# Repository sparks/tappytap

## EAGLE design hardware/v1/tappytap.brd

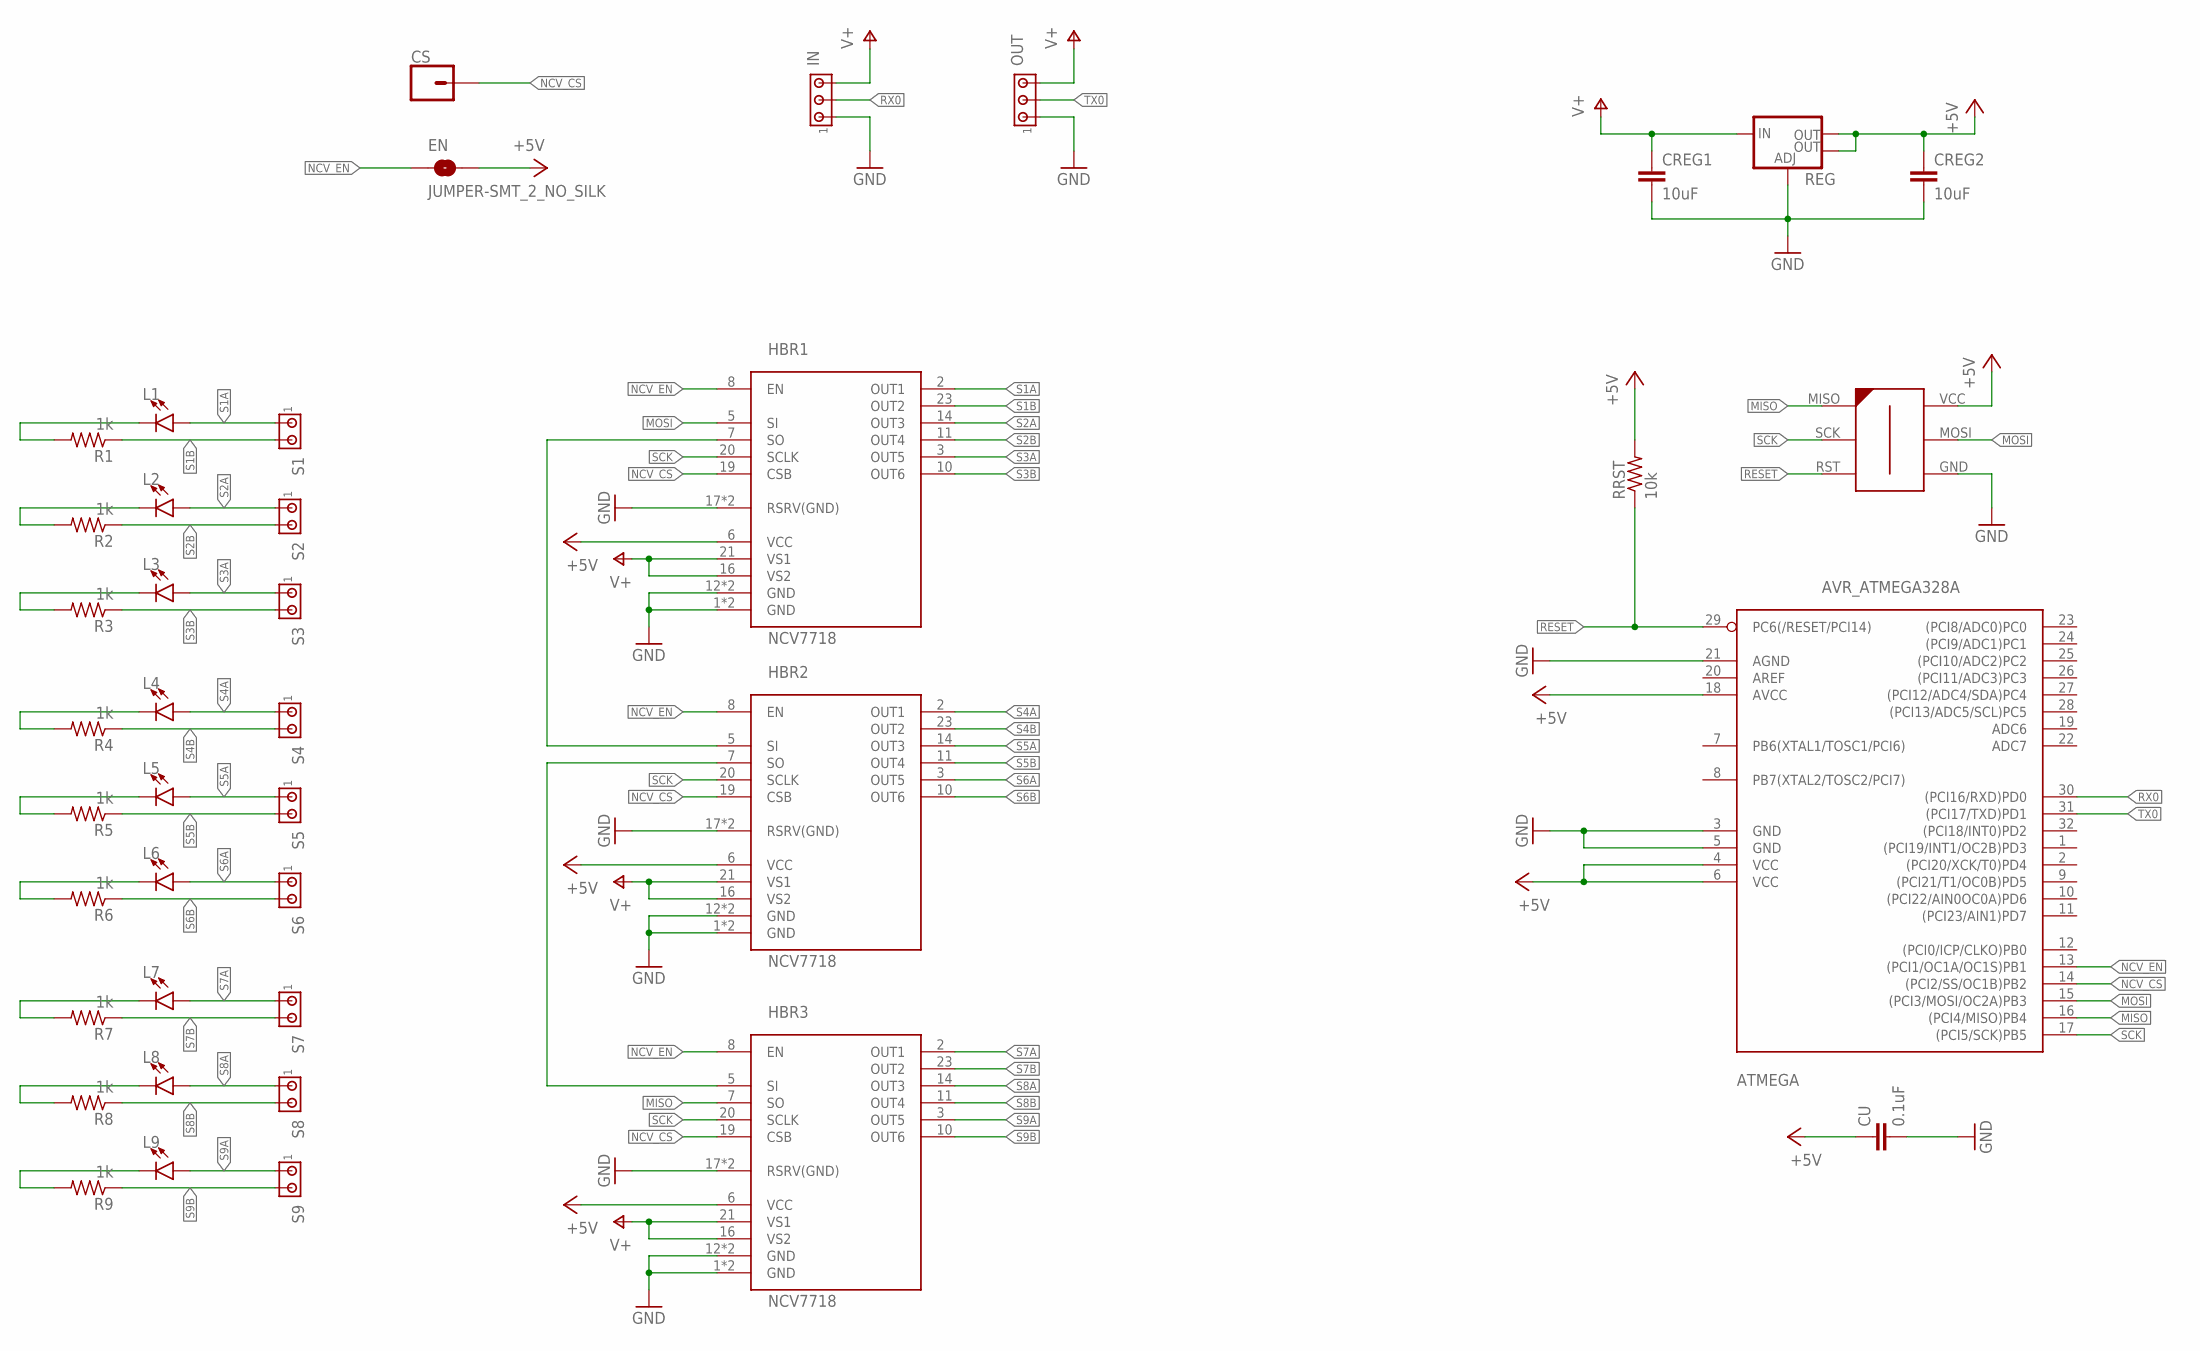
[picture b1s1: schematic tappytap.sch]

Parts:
ATMEGA: AVR_ATMEGA328A; AVR_TQFP32-08
CREG1, CREG2: 10uF; C0603
CS: CONN_01; 1X01
CU: 0.1uF; C0603
EN: JUMPER-SMT_2_NO_SILK; SMT-JUMPER_2_NO_SILK
HBR1, HBR2, HBR3: NCV7718; 24-SSOP
IN: MTA03-100; 10X03MTA
ISP: AVR-ISP-6-EDGE; 6PAD_ISP
L1, L2, L3, L4, L5, L6, L7, L8, L9: LED0603; LED-0603
OUT: MTA03-100; 10X03MTA
R1, R2, R3, R4, R5, R6, R7, R8, R9: 1k; R0603
REG: V_REG_LM1117SOT223; SOT223
RRST: 10k; R0603
S1, S2, S3, S4, S5, S6, S7, S8, S9: MTA02-100; 10X02MTA

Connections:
+5V: ATMEGA.4 (VCC), ATMEGA.6 (VCC), ATMEGA.18 (AVCC), CREG2.1, CU.1, EN.2, HBR1.6 (VCC), HBR2.6 (VCC), HBR3.6 (VCC), ISP.VCC, REG.2 (OUT), REG.4 (OUT), RRST.2
GND: ATMEGA.3 (GND), ATMEGA.5 (GND), ATMEGA.21 (AGND), CREG1.2, CREG2.2, CU.2, HBR1.1 (GND), HBR1.12 (GND), HBR1.13 (GND), HBR1.17 (RSRV(GND)), HBR1.18 (RSRV(GND)), HBR1.24 (GND), HBR2.1 (GND), HBR2.12 (GND), HBR2.13 (GND), HBR2.17 (RSRV(GND)), HBR2.18 (RSRV(GND)), HBR2.24 (GND), HBR3.1 (GND), HBR3.12 (GND), HBR3.13 (GND), HBR3.17 (RSRV(GND)), HBR3.18 (RSRV(GND)), HBR3.24 (GND), IN.1, ISP.GND, OUT.1, REG.1 (ADJ)
MISO: ATMEGA.16 ((PCI4/MISO)PB4), HBR3.7 (SO), ISP.MISO
MOSI: ATMEGA.15 ((PCI3/MOSI/OC2A)PB3), HBR1.5 (SI), ISP.MOSI
unnamed: L1.C, R1.2
unnamed: L2.C, R2.2
unnamed: L3.C, R3.2
unnamed: L4.C, R4.2
unnamed: L5.C, R5.2
unnamed: L6.C, R6.2
unnamed: HBR1.7 (SO), HBR2.5 (SI)
unnamed: L7.C, R7.2
unnamed: HBR2.7 (SO), HBR3.5 (SI)
unnamed: L8.C, R8.2
unnamed: L9.C, R9.2
NCV_CS: ATMEGA.14 ((PCI2/SS/OC1B)PB2), CS.1, HBR1.19 (CSB), HBR2.19 (CSB), HBR3.19 (CSB)
NCV_EN: ATMEGA.13 ((PCI1/OC1A/OC1S)PB1), EN.1, HBR1.8 (EN), HBR2.8 (EN), HBR3.8 (EN)
RESET: ATMEGA.29 (PC6(/RESET/PCI14)), ISP.RST, RRST.1
RX0: ATMEGA.30 ((PCI16/RXD)PD0), IN.2
S1A: HBR1.2 (OUT1), L1.A, S1.1
S1B: HBR1.23 (OUT2), R1.1, S1.2
S2A: HBR1.14 (OUT3), L2.A, S2.1
S2B: HBR1.11 (OUT4), R2.1, S2.2
S3A: HBR1.3 (OUT5), L3.A, S3.1
S3B: HBR1.10 (OUT6), R3.1, S3.2
S4A: HBR2.2 (OUT1), L4.A, S4.1
S4B: HBR2.23 (OUT2), R4.1, S4.2
S5A: HBR2.14 (OUT3), L5.A, S5.1
S5B: HBR2.11 (OUT4), R5.1, S5.2
S6A: HBR2.3 (OUT5), L6.A, S6.1
S6B: HBR2.10 (OUT6), R6.1, S6.2
S7A: HBR3.2 (OUT1), L7.A, S7.1
S7B: HBR3.23 (OUT2), R7.1, S7.2
S8A: HBR3.14 (OUT3), L8.A, S8.1
S8B: HBR3.11 (OUT4), R8.1, S8.2
S9A: HBR3.3 (OUT5), L9.A, S9.1
S9B: HBR3.10 (OUT6), R9.1, S9.2
SCK: ATMEGA.17 ((PCI5/SCK)PB5), HBR1.20 (SCLK), HBR2.20 (SCLK), HBR3.20 (SCLK), ISP.SCK
TX0: ATMEGA.31 ((PCI17/TXD)PD1), OUT.2
V+: CREG1.1, HBR1.16 (VS2), HBR1.21 (VS1), HBR2.16 (VS2), HBR2.21 (VS1), HBR3.16 (VS2), HBR3.21 (VS1), IN.3, OUT.3, REG.3 (IN)

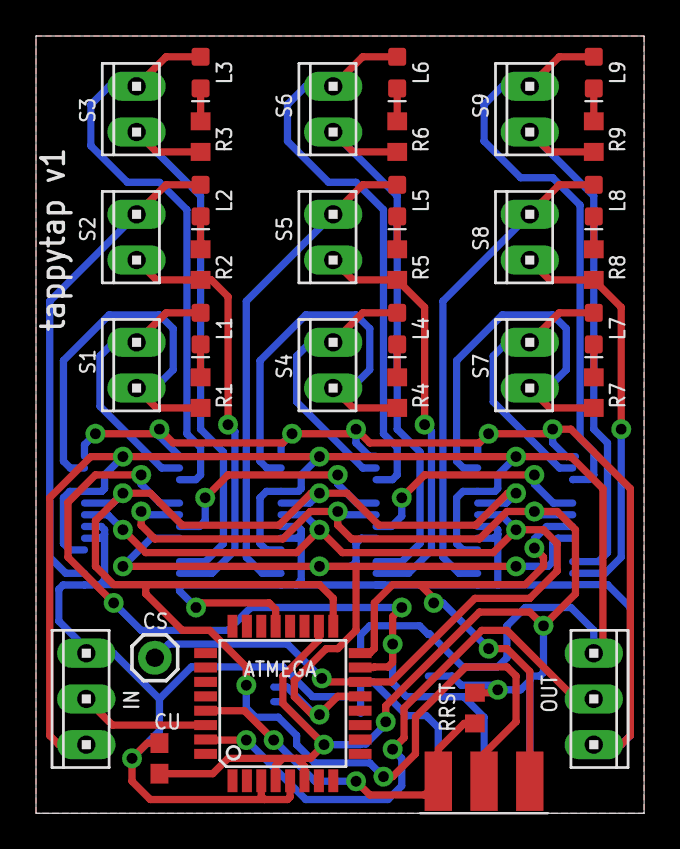
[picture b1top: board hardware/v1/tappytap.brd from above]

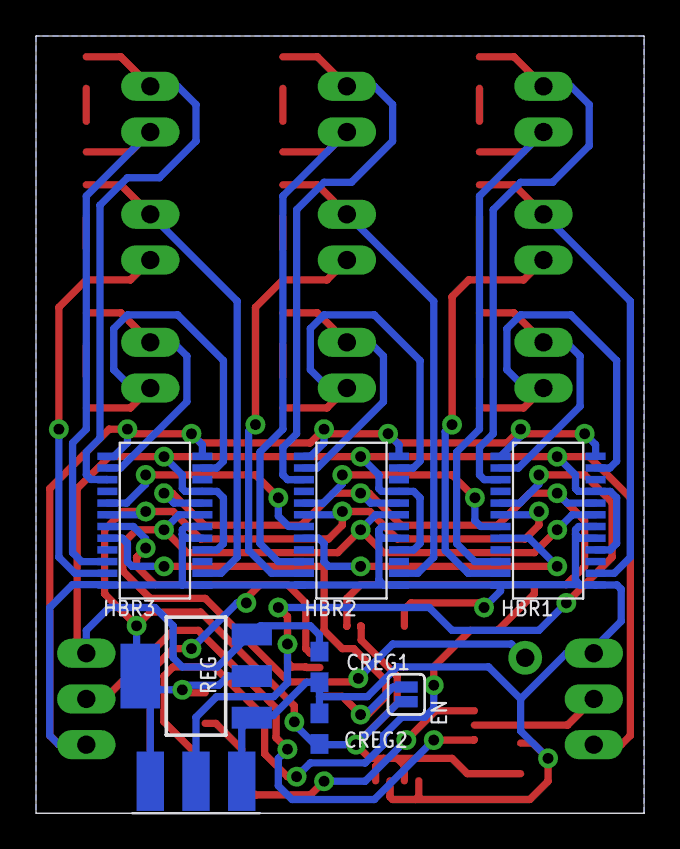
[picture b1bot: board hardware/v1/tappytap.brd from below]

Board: 2 copper layers, 33.8 x 43.2 mm, 41 parts (7 on the bottom side), 40 nets.

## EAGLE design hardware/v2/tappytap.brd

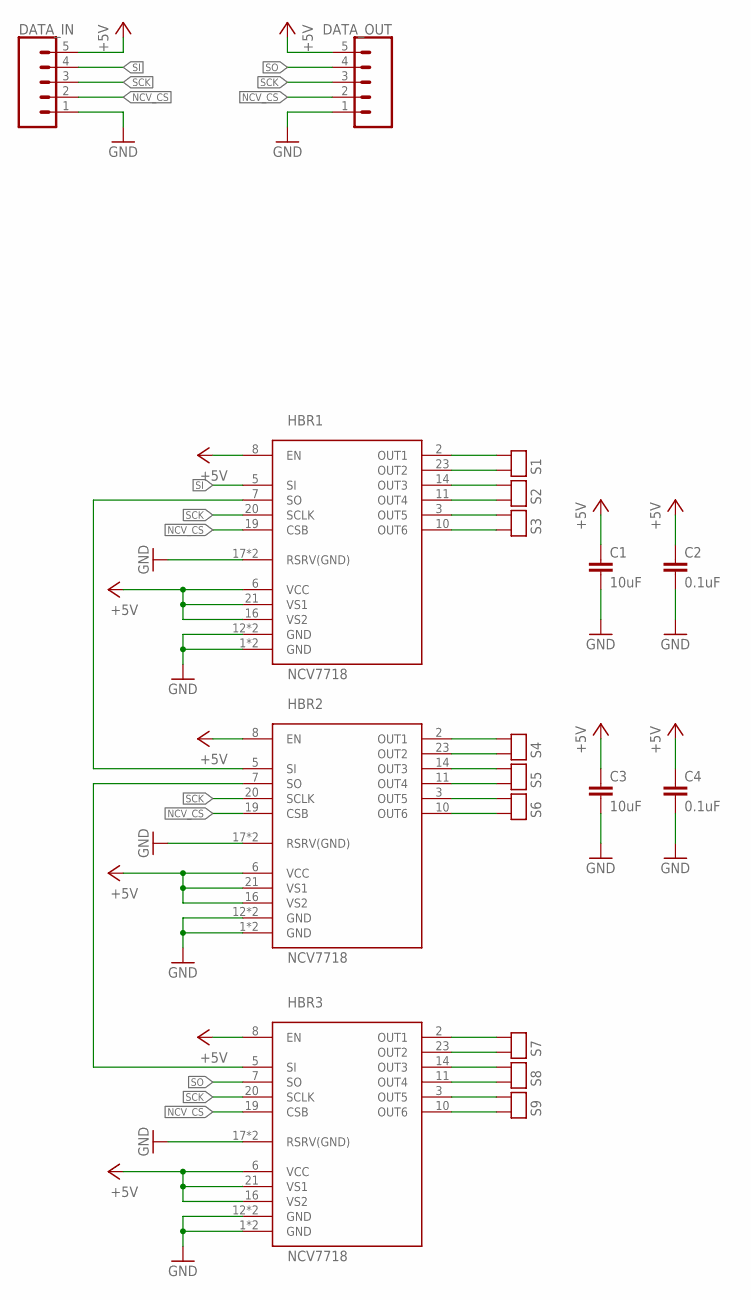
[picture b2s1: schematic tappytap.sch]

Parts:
C1, C3: 10uF; C0603
C2, C4: 0.1uF; C0603
DATA_IN: CONN_05; 1X05
DATA_OUT: CONN_05; 1X05
HBR1, HBR2, HBR3: NCV7718; 24-SSOP
S1, S2, S3, S4, S5, S6, S7, S8, S9: TP2; TP2_2MM

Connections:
+5V: C1.1, C2.1, C3.1, C4.1, DATA_IN.5, DATA_OUT.5, HBR1.6 (VCC), HBR1.8 (EN), HBR1.16 (VS2), HBR1.21 (VS1), HBR2.6 (VCC), HBR2.8 (EN), HBR2.16 (VS2), HBR2.21 (VS1), HBR3.6 (VCC), HBR3.8 (EN), HBR3.16 (VS2), HBR3.21 (VS1)
GND: C1.2, C2.2, C3.2, C4.2, DATA_IN.1, DATA_OUT.1, HBR1.1 (GND), HBR1.12 (GND), HBR1.13 (GND), HBR1.17 (RSRV(GND)), HBR1.18 (RSRV(GND)), HBR1.24 (GND), HBR2.1 (GND), HBR2.12 (GND), HBR2.13 (GND), HBR2.17 (RSRV(GND)), HBR2.18 (RSRV(GND)), HBR2.24 (GND), HBR3.1 (GND), HBR3.12 (GND), HBR3.13 (GND), HBR3.17 (RSRV(GND)), HBR3.18 (RSRV(GND)), HBR3.24 (GND)
unnamed: HBR1.7 (SO), HBR2.5 (SI)
unnamed: HBR2.7 (SO), HBR3.5 (SI)
NCV_CS: DATA_IN.2, DATA_OUT.2, HBR1.19 (CSB), HBR2.19 (CSB), HBR3.19 (CSB)
S1A: HBR1.2 (OUT1), S1.P$1 (0)
S1B: HBR1.23 (OUT2), S1.P$2 (1)
S2A: HBR1.14 (OUT3), S2.P$1 (0)
S2B: HBR1.11 (OUT4), S2.P$2 (1)
S3A: HBR1.3 (OUT5), S3.P$1 (0)
S3B: HBR1.10 (OUT6), S3.P$2 (1)
S4A: HBR2.2 (OUT1), S4.P$1 (0)
S4B: HBR2.23 (OUT2), S4.P$2 (1)
S5A: HBR2.14 (OUT3), S5.P$1 (0)
S5B: HBR2.11 (OUT4), S5.P$2 (1)
S6A: HBR2.3 (OUT5), S6.P$1 (0)
S6B: HBR2.10 (OUT6), S6.P$2 (1)
S7A: HBR3.2 (OUT1), S7.P$1 (0)
S7B: HBR3.23 (OUT2), S7.P$2 (1)
S8A: HBR3.14 (OUT3), S8.P$1 (0)
S8B: HBR3.11 (OUT4), S8.P$2 (1)
S9A: HBR3.3 (OUT5), S9.P$1 (0)
S9B: HBR3.10 (OUT6), S9.P$2 (1)
SCK: DATA_IN.3, DATA_OUT.3, HBR1.20 (SCLK), HBR2.20 (SCLK), HBR3.20 (SCLK)
SI: DATA_IN.4, HBR1.5 (SI)
SO: DATA_OUT.4, HBR3.7 (SO)

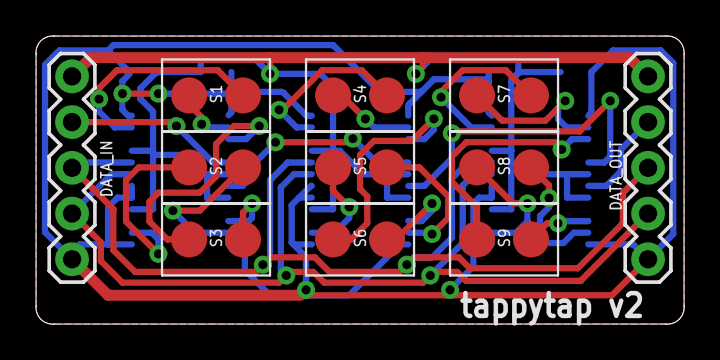
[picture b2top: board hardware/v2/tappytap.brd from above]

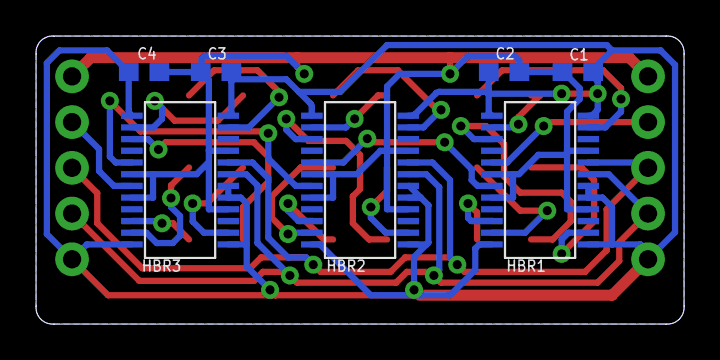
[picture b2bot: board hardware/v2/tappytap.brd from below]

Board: 2 copper layers, 36.0 x 16.0 mm, 18 parts (7 on the bottom side), 26 nets.

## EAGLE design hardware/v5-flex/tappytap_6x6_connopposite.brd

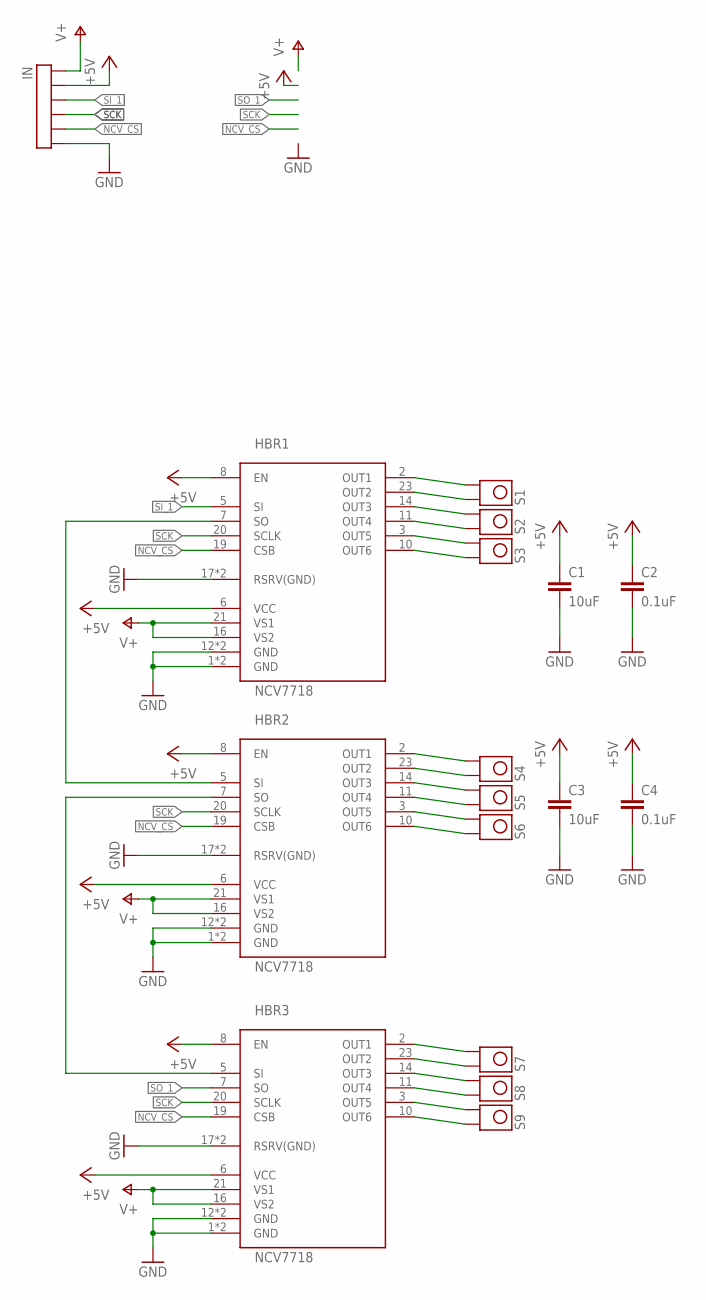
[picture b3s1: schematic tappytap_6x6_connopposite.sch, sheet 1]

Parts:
C1, C3: 10uF; C0603
C2, C4: 0.1uF; C0603
HBR1, HBR2, HBR3: NCV7718; SSOP-24
IN: TP6; TP6_2MM
S1, S2, S3, S4, S5, S6, S7, S8, S9: TP_6MM_BIG_PAD

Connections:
+5V: C1.1, C2.1, C3.1, C4.1, HBR1.6 (VCC), HBR1.8 (EN), HBR2.6 (VCC), HBR2.8 (EN), HBR3.6 (VCC), HBR3.8 (EN), IN.P$5 (5); also elsewhere on the board
GND: C1.2, C2.2, C3.2, C4.2, HBR1.1 (GND), HBR1.12 (GND), HBR1.13 (GND), HBR1.17 (RSRV(GND)), HBR1.18 (RSRV(GND)), HBR1.24 (GND), HBR2.1 (GND), HBR2.12 (GND), HBR2.13 (GND), HBR2.17 (RSRV(GND)), HBR2.18 (RSRV(GND)), HBR2.24 (GND), HBR3.1 (GND), HBR3.12 (GND), HBR3.13 (GND), HBR3.17 (RSRV(GND)), HBR3.18 (RSRV(GND)), HBR3.24 (GND), IN.P$1 (1); also elsewhere on the board
unnamed: HBR1.7 (SO), HBR2.5 (SI)
unnamed: HBR2.7 (SO), HBR3.5 (SI)
NCV_CS: HBR1.19 (CSB), HBR2.19 (CSB), HBR3.19 (CSB), IN.P$2 (2); also elsewhere on the board
S1A: HBR1.2 (OUT1), S1.P$1 (0)
S1B: HBR1.23 (OUT2), S1.P$2 (1)
S2A: HBR1.14 (OUT3), S2.P$1 (0)
S2B: HBR1.11 (OUT4), S2.P$2 (1)
S3A: HBR1.3 (OUT5), S3.P$1 (0)
S3B: HBR1.10 (OUT6), S3.P$2 (1)
S4A: HBR2.2 (OUT1), S4.P$1 (0)
S4B: HBR2.23 (OUT2), S4.P$2 (1)
S5A: HBR2.14 (OUT3), S5.P$1 (0)
S5B: HBR2.11 (OUT4), S5.P$2 (1)
S6A: HBR2.3 (OUT5), S6.P$1 (0)
S6B: HBR2.10 (OUT6), S6.P$2 (1)
S7A: HBR3.2 (OUT1), S7.P$1 (0)
S7B: HBR3.23 (OUT2), S7.P$2 (1)
S8A: HBR3.14 (OUT3), S8.P$1 (0)
S8B: HBR3.11 (OUT4), S8.P$2 (1)
S9A: HBR3.3 (OUT5), S9.P$1 (0)
S9B: HBR3.10 (OUT6), S9.P$2 (1)
SCK: HBR1.20 (SCLK), HBR2.20 (SCLK), HBR3.20 (SCLK), IN.P$3 (3); also elsewhere on the board
SI_1: HBR1.5 (SI), IN.P$4 (4)
SO_1: HBR3.7 (SO); also elsewhere on the board
V+: HBR1.16 (VS2), HBR1.21 (VS1), HBR2.16 (VS2), HBR2.21 (VS1), HBR3.16 (VS2), HBR3.21 (VS1), IN.P$6 (6); also elsewhere on the board

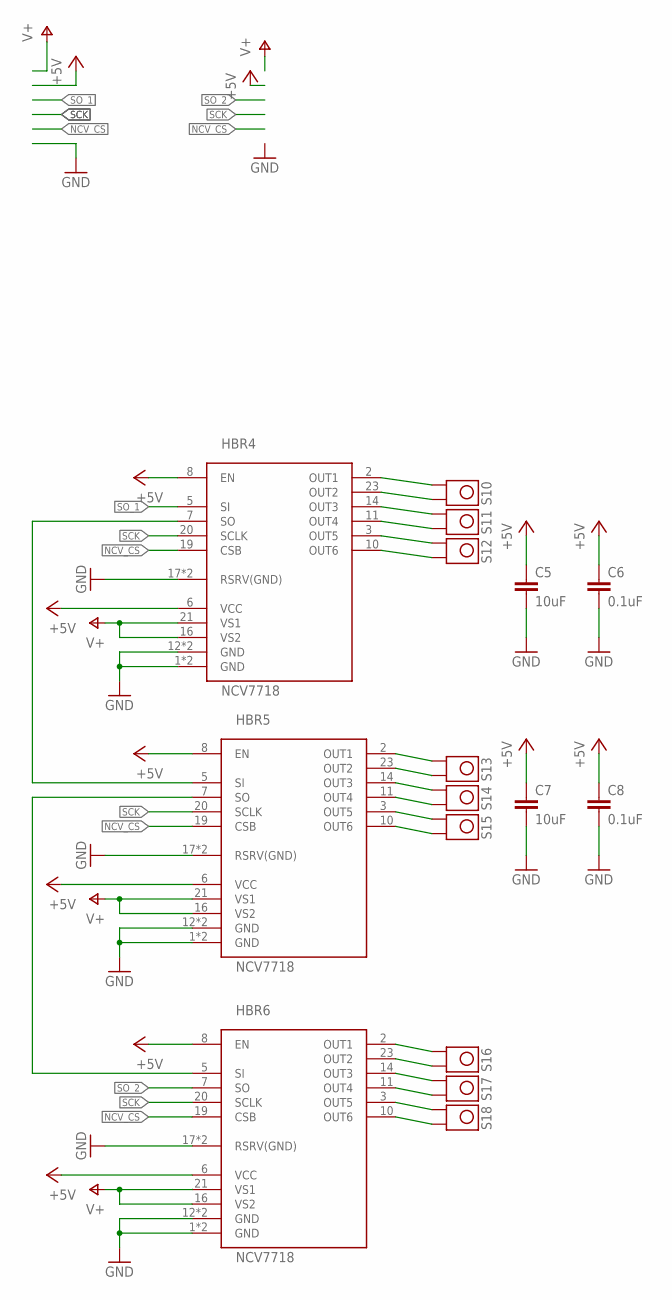
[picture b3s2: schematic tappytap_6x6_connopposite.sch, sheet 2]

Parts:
C5, C7: 10uF; C0603
C6, C8: 0.1uF; C0603
HBR4, HBR5, HBR6: NCV7718; SSOP-24
S10, S11, S12, S13, S14, S15, S16, S17, S18: TP_6MM_BIG_PAD

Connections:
+5V: C5.1, C6.1, C7.1, C8.1, HBR4.6 (VCC), HBR4.8 (EN), HBR5.6 (VCC), HBR5.8 (EN), HBR6.6 (VCC), HBR6.8 (EN); also elsewhere on the board
GND: C5.2, C6.2, C7.2, C8.2, HBR4.1 (GND), HBR4.12 (GND), HBR4.13 (GND), HBR4.17 (RSRV(GND)), HBR4.18 (RSRV(GND)), HBR4.24 (GND), HBR5.1 (GND), HBR5.12 (GND), HBR5.13 (GND), HBR5.17 (RSRV(GND)), HBR5.18 (RSRV(GND)), HBR5.24 (GND), HBR6.1 (GND), HBR6.12 (GND), HBR6.13 (GND), HBR6.17 (RSRV(GND)), HBR6.18 (RSRV(GND)), HBR6.24 (GND); also elsewhere on the board
unnamed: HBR4.7 (SO), HBR5.5 (SI)
unnamed: HBR5.7 (SO), HBR6.5 (SI)
NCV_CS: HBR4.19 (CSB), HBR5.19 (CSB), HBR6.19 (CSB); also elsewhere on the board
S1A1: HBR4.2 (OUT1), S10.P$1 (0)
S1B1: HBR4.23 (OUT2), S10.P$2 (1)
S2A1: HBR4.14 (OUT3), S11.P$1 (0)
S2B1: HBR4.11 (OUT4), S11.P$2 (1)
S3A1: HBR4.3 (OUT5), S12.P$1 (0)
S3B1: HBR4.10 (OUT6), S12.P$2 (1)
S4A1: HBR5.2 (OUT1), S13.P$1 (0)
S4B1: HBR5.23 (OUT2), S13.P$2 (1)
S5A1: HBR5.14 (OUT3), S14.P$1 (0)
S5B1: HBR5.11 (OUT4), S14.P$2 (1)
S6A1: HBR5.3 (OUT5), S15.P$1 (0)
S6B1: HBR5.10 (OUT6), S15.P$2 (1)
S7A1: HBR6.2 (OUT1), S16.P$1 (0)
S7B1: HBR6.23 (OUT2), S16.P$2 (1)
S8A1: HBR6.14 (OUT3), S17.P$1 (0)
S8B1: HBR6.11 (OUT4), S17.P$2 (1)
S9A1: HBR6.3 (OUT5), S18.P$1 (0)
S9B1: HBR6.10 (OUT6), S18.P$2 (1)
SCK: HBR4.20 (SCLK), HBR5.20 (SCLK), HBR6.20 (SCLK); also elsewhere on the board
SO_1: HBR4.5 (SI); also elsewhere on the board
SO_2: HBR6.7 (SO); also elsewhere on the board
V+: HBR4.16 (VS2), HBR4.21 (VS1), HBR5.16 (VS2), HBR5.21 (VS1), HBR6.16 (VS2), HBR6.21 (VS1); also elsewhere on the board

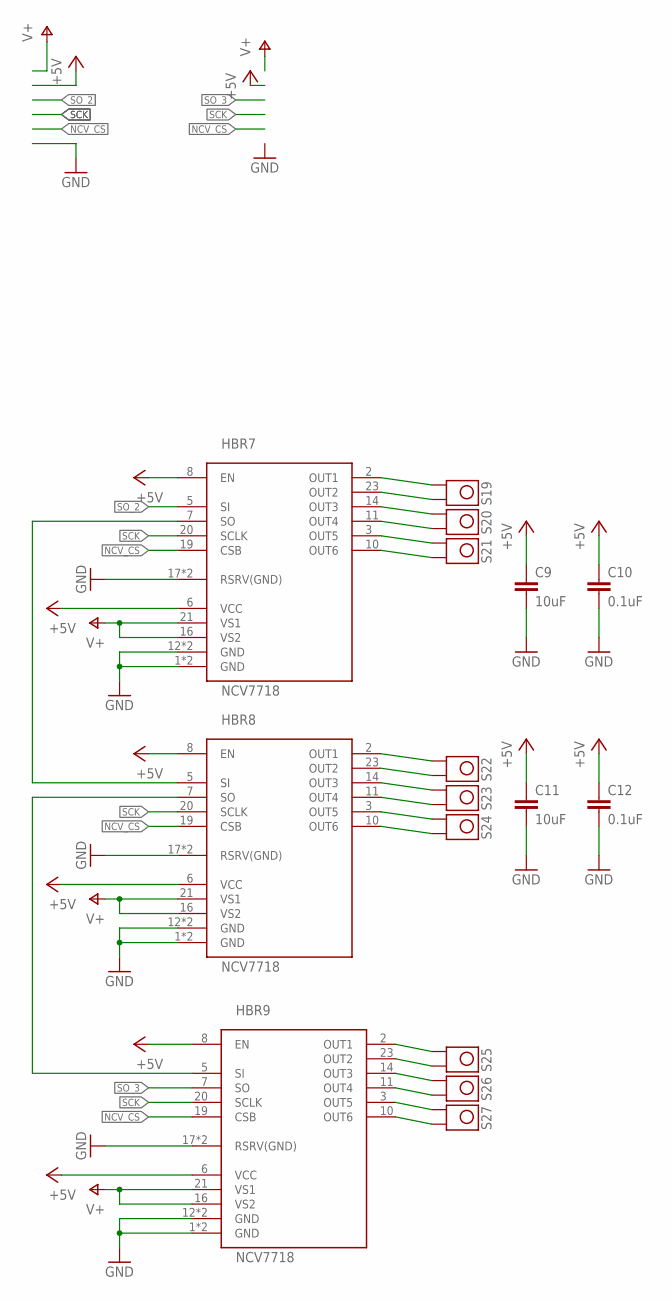
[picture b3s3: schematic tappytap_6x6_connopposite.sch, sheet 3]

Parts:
C9, C11: 10uF; C0603
C10, C12: 0.1uF; C0603
HBR7, HBR8, HBR9: NCV7718; SSOP-24
S19, S20, S21, S22, S23, S24, S25, S26, S27: TP_6MM_BIG_PAD

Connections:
+5V: C9.1, C10.1, C11.1, C12.1, HBR7.6 (VCC), HBR7.8 (EN), HBR8.6 (VCC), HBR8.8 (EN), HBR9.6 (VCC), HBR9.8 (EN); also elsewhere on the board
GND: C9.2, C10.2, C11.2, C12.2, HBR7.1 (GND), HBR7.12 (GND), HBR7.13 (GND), HBR7.17 (RSRV(GND)), HBR7.18 (RSRV(GND)), HBR7.24 (GND), HBR8.1 (GND), HBR8.12 (GND), HBR8.13 (GND), HBR8.17 (RSRV(GND)), HBR8.18 (RSRV(GND)), HBR8.24 (GND), HBR9.1 (GND), HBR9.12 (GND), HBR9.13 (GND), HBR9.17 (RSRV(GND)), HBR9.18 (RSRV(GND)), HBR9.24 (GND); also elsewhere on the board
unnamed: HBR7.7 (SO), HBR8.5 (SI)
unnamed: HBR8.7 (SO), HBR9.5 (SI)
NCV_CS: HBR7.19 (CSB), HBR8.19 (CSB), HBR9.19 (CSB); also elsewhere on the board
S1A2: HBR7.2 (OUT1), S19.P$1 (0)
S1B2: HBR7.23 (OUT2), S19.P$2 (1)
S2A2: HBR7.14 (OUT3), S20.P$1 (0)
S2B2: HBR7.11 (OUT4), S20.P$2 (1)
S3A2: HBR7.3 (OUT5), S21.P$1 (0)
S3B2: HBR7.10 (OUT6), S21.P$2 (1)
S4A2: HBR8.2 (OUT1), S22.P$1 (0)
S4B2: HBR8.23 (OUT2), S22.P$2 (1)
S5A2: HBR8.14 (OUT3), S23.P$1 (0)
S5B2: HBR8.11 (OUT4), S23.P$2 (1)
S6A2: HBR8.3 (OUT5), S24.P$1 (0)
S6B2: HBR8.10 (OUT6), S24.P$2 (1)
S7A2: HBR9.2 (OUT1), S25.P$1 (0)
S7B2: HBR9.23 (OUT2), S25.P$2 (1)
S8A2: HBR9.14 (OUT3), S26.P$1 (0)
S8B2: HBR9.11 (OUT4), S26.P$2 (1)
S9A2: HBR9.3 (OUT5), S27.P$1 (0)
S9B2: HBR9.10 (OUT6), S27.P$2 (1)
SCK: HBR7.20 (SCLK), HBR8.20 (SCLK), HBR9.20 (SCLK); also elsewhere on the board
SO_2: HBR7.5 (SI); also elsewhere on the board
SO_3: HBR9.7 (SO); also elsewhere on the board
V+: HBR7.16 (VS2), HBR7.21 (VS1), HBR8.16 (VS2), HBR8.21 (VS1), HBR9.16 (VS2), HBR9.21 (VS1); also elsewhere on the board

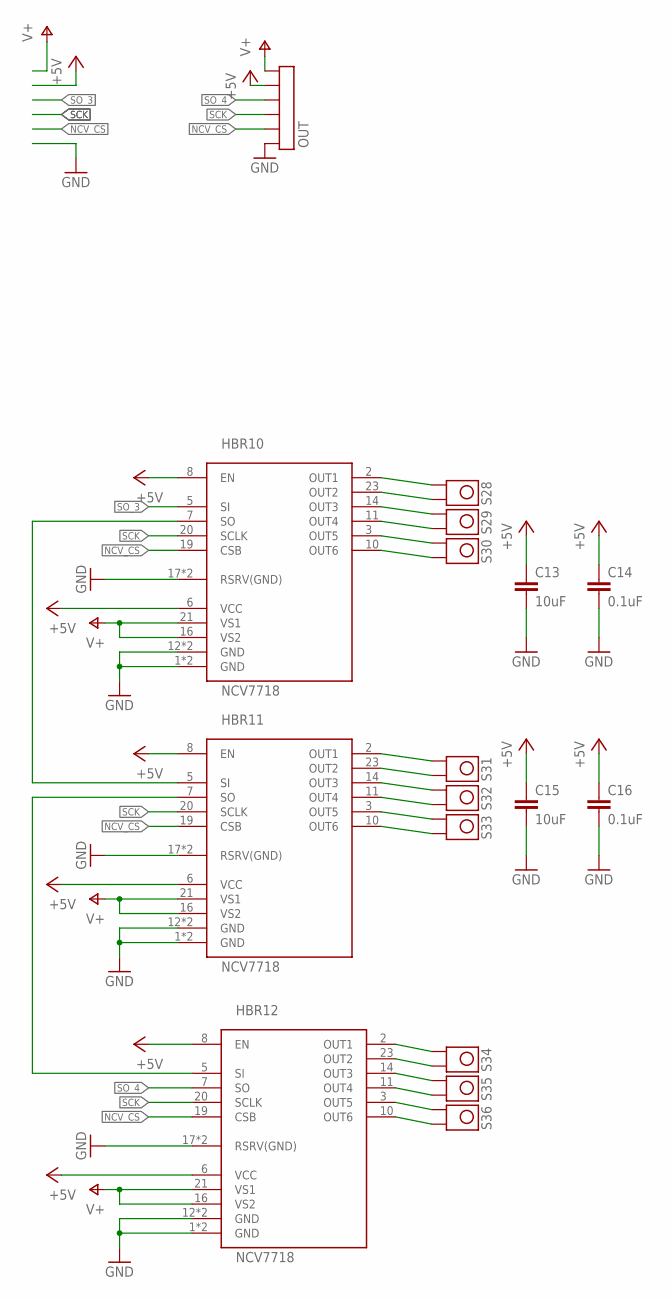
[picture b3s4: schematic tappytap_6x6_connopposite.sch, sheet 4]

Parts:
C13, C15: 10uF; C0603
C14, C16: 0.1uF; C0603
HBR10, HBR11, HBR12: NCV7718; SSOP-24
OUT: TP6; TP6_2MM
S28, S29, S30, S31, S32, S33, S34, S35, S36: TP_6MM_BIG_PAD

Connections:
+5V: C13.1, C14.1, C15.1, C16.1, HBR10.6 (VCC), HBR10.8 (EN), HBR11.6 (VCC), HBR11.8 (EN), HBR12.6 (VCC), HBR12.8 (EN), OUT.P$2 (2); also elsewhere on the board
GND: C13.2, C14.2, C15.2, C16.2, HBR10.1 (GND), HBR10.12 (GND), HBR10.13 (GND), HBR10.17 (RSRV(GND)), HBR10.18 (RSRV(GND)), HBR10.24 (GND), HBR11.1 (GND), HBR11.12 (GND), HBR11.13 (GND), HBR11.17 (RSRV(GND)), HBR11.18 (RSRV(GND)), HBR11.24 (GND), HBR12.1 (GND), HBR12.12 (GND), HBR12.13 (GND), HBR12.17 (RSRV(GND)), HBR12.18 (RSRV(GND)), HBR12.24 (GND), OUT.P$6 (6); also elsewhere on the board
unnamed: HBR10.7 (SO), HBR11.5 (SI)
unnamed: HBR11.7 (SO), HBR12.5 (SI)
NCV_CS: HBR10.19 (CSB), HBR11.19 (CSB), HBR12.19 (CSB), OUT.P$5 (5); also elsewhere on the board
S1A3: HBR10.2 (OUT1), S28.P$1 (0)
S1B3: HBR10.23 (OUT2), S28.P$2 (1)
S2A3: HBR10.14 (OUT3), S29.P$1 (0)
S2B3: HBR10.11 (OUT4), S29.P$2 (1)
S3A3: HBR10.3 (OUT5), S30.P$1 (0)
S3B3: HBR10.10 (OUT6), S30.P$2 (1)
S4A3: HBR11.2 (OUT1), S31.P$1 (0)
S4B3: HBR11.23 (OUT2), S31.P$2 (1)
S5A3: HBR11.14 (OUT3), S32.P$1 (0)
S5B3: HBR11.11 (OUT4), S32.P$2 (1)
S6A3: HBR11.3 (OUT5), S33.P$1 (0)
S6B3: HBR11.10 (OUT6), S33.P$2 (1)
S7A3: HBR12.2 (OUT1), S34.P$1 (0)
S7B3: HBR12.23 (OUT2), S34.P$2 (1)
S8A3: HBR12.14 (OUT3), S35.P$1 (0)
S8B3: HBR12.11 (OUT4), S35.P$2 (1)
S9A3: HBR12.3 (OUT5), S36.P$1 (0)
S9B3: HBR12.10 (OUT6), S36.P$2 (1)
SCK: HBR10.20 (SCLK), HBR11.20 (SCLK), HBR12.20 (SCLK), OUT.P$4 (4); also elsewhere on the board
SO_3: HBR10.5 (SI); also elsewhere on the board
SO_4: HBR12.7 (SO), OUT.P$3 (3)
V+: HBR10.16 (VS2), HBR10.21 (VS1), HBR11.16 (VS2), HBR11.21 (VS1), HBR12.16 (VS2), HBR12.21 (VS1), OUT.P$1 (1); also elsewhere on the board

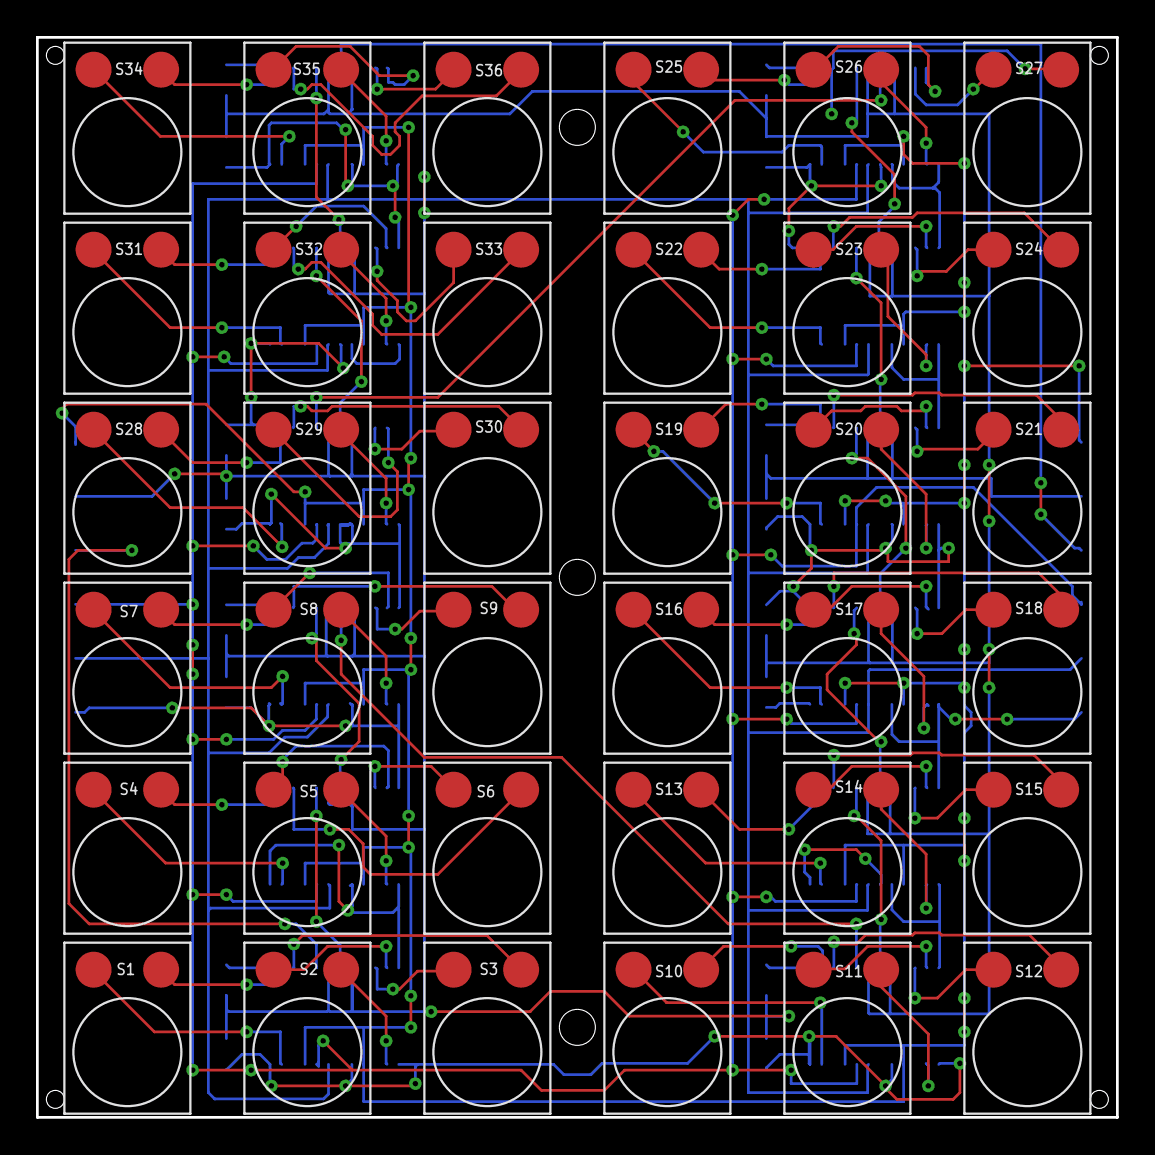
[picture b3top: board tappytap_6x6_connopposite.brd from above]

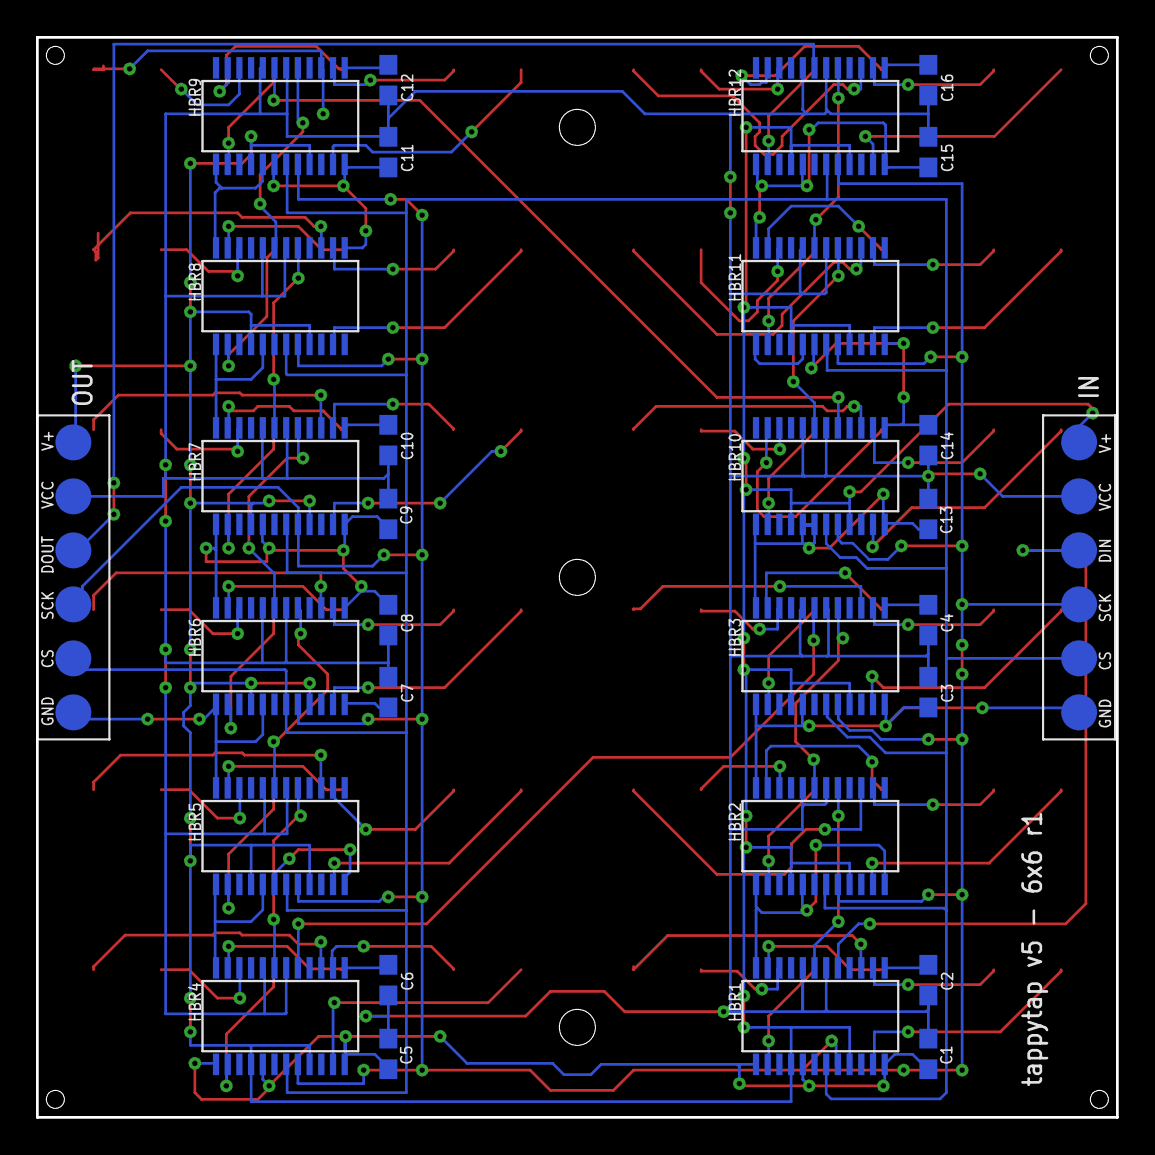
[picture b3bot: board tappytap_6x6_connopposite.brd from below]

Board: 2 copper layers, 60.0 x 60.0 mm, 66 parts (30 on the bottom side), 90 nets.

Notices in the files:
parts and their libraries:
SparkFun-LED: Licensing: Creative Commons ShareAlike 4.0 International - https://creativecommons.org/licenses/by-sa/4.0
